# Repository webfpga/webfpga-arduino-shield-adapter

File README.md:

WebFPGA Arduino Shield Adapater
===============================

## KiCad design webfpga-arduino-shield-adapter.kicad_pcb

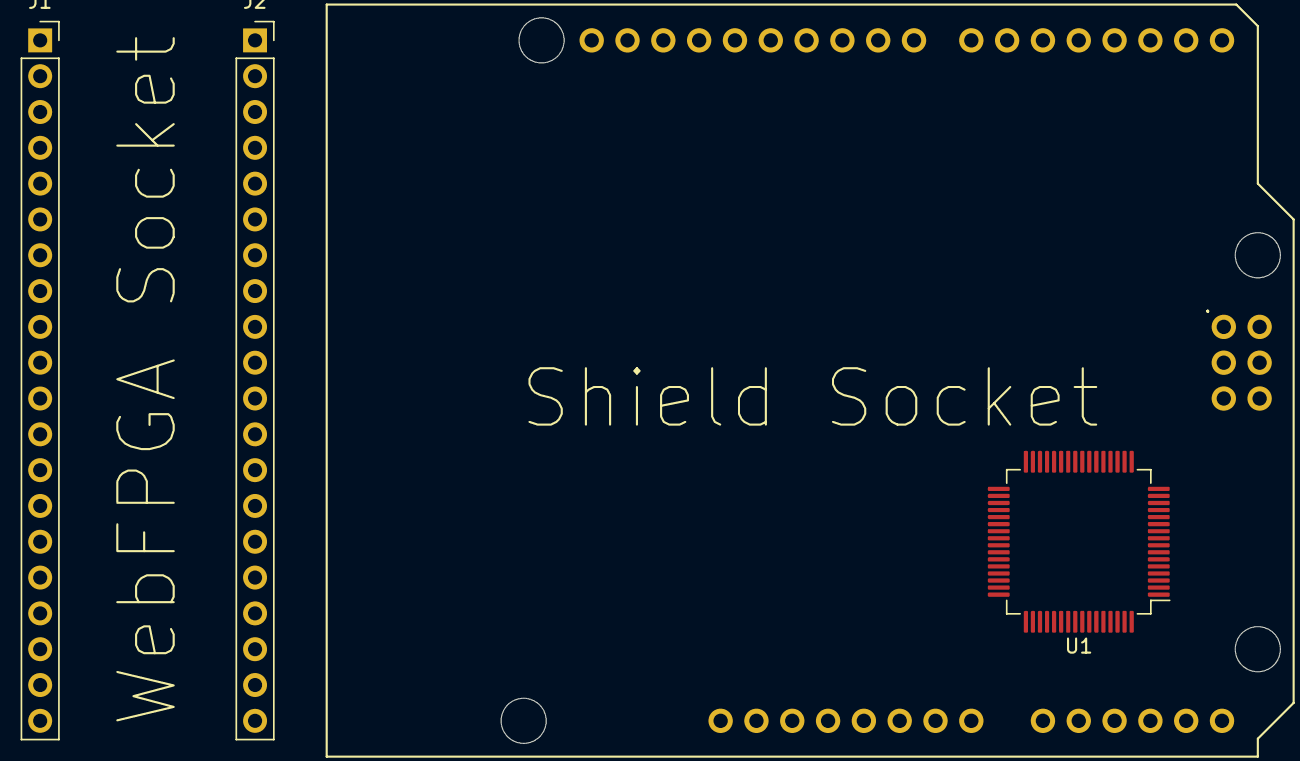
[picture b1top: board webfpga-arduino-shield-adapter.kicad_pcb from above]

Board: 2 copper layers, 4 parts (0 on the bottom side), 10 nets, no tracks yet.

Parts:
J1, J2: Conn_01x20_Female; PinSocket_1x20_P2.54mm_Vertical
U1: AD7606-6; LQFP-64_10x10mm_P0.5mm
XA1: Arduino_Uno_Shield

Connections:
+5V: XA1.5V1, XA1.VIN
/A0: U1.49, XA1.A0
/A1: U1.51, XA1.A1
/A2: U1.53, XA1.A2
/A3: U1.57, XA1.A3
/A4: U1.59, XA1.A4
/A5: U1.61, XA1.A5
GND: U1.50, U1.52, U1.54, U1.58, U1.60, U1.62, XA1.AREF, XA1.GND1, XA1.GND2, XA1.GND3
unnamed: U1.2, U1.26, U1.35, U1.40, U1.41, U1.47, U1.55, U1.56, U1.63, U1.64
unnamed: U1.43, U1.46

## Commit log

2019-07-08 git init
2019-07-08 render
